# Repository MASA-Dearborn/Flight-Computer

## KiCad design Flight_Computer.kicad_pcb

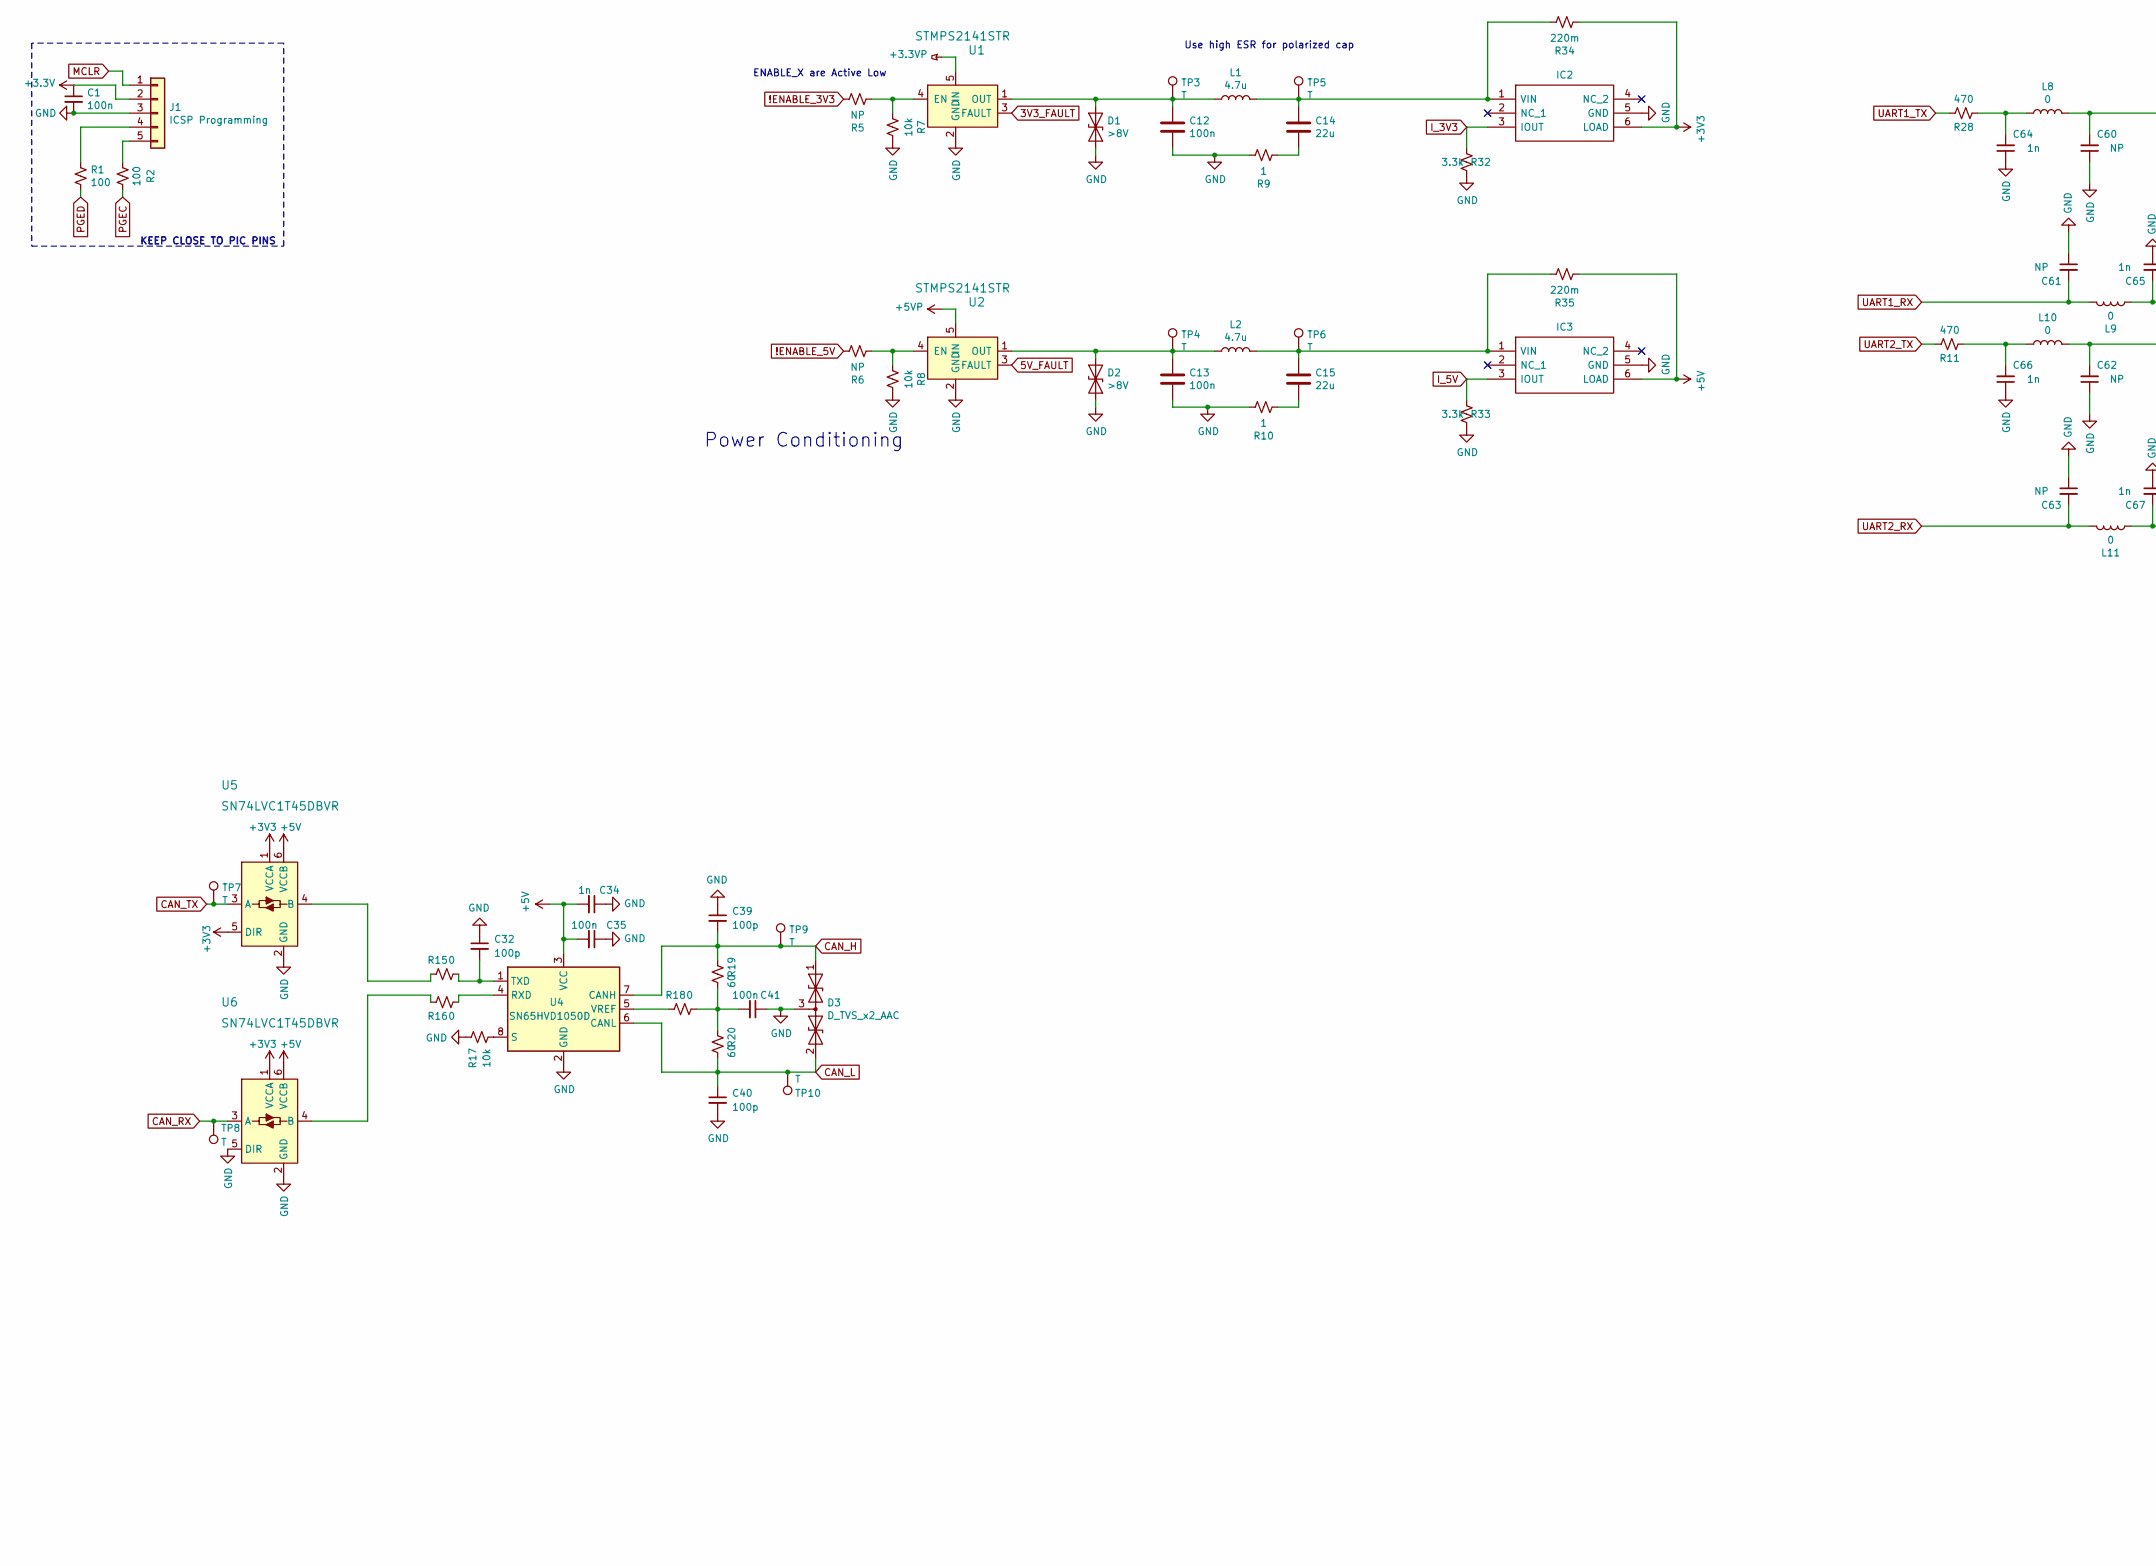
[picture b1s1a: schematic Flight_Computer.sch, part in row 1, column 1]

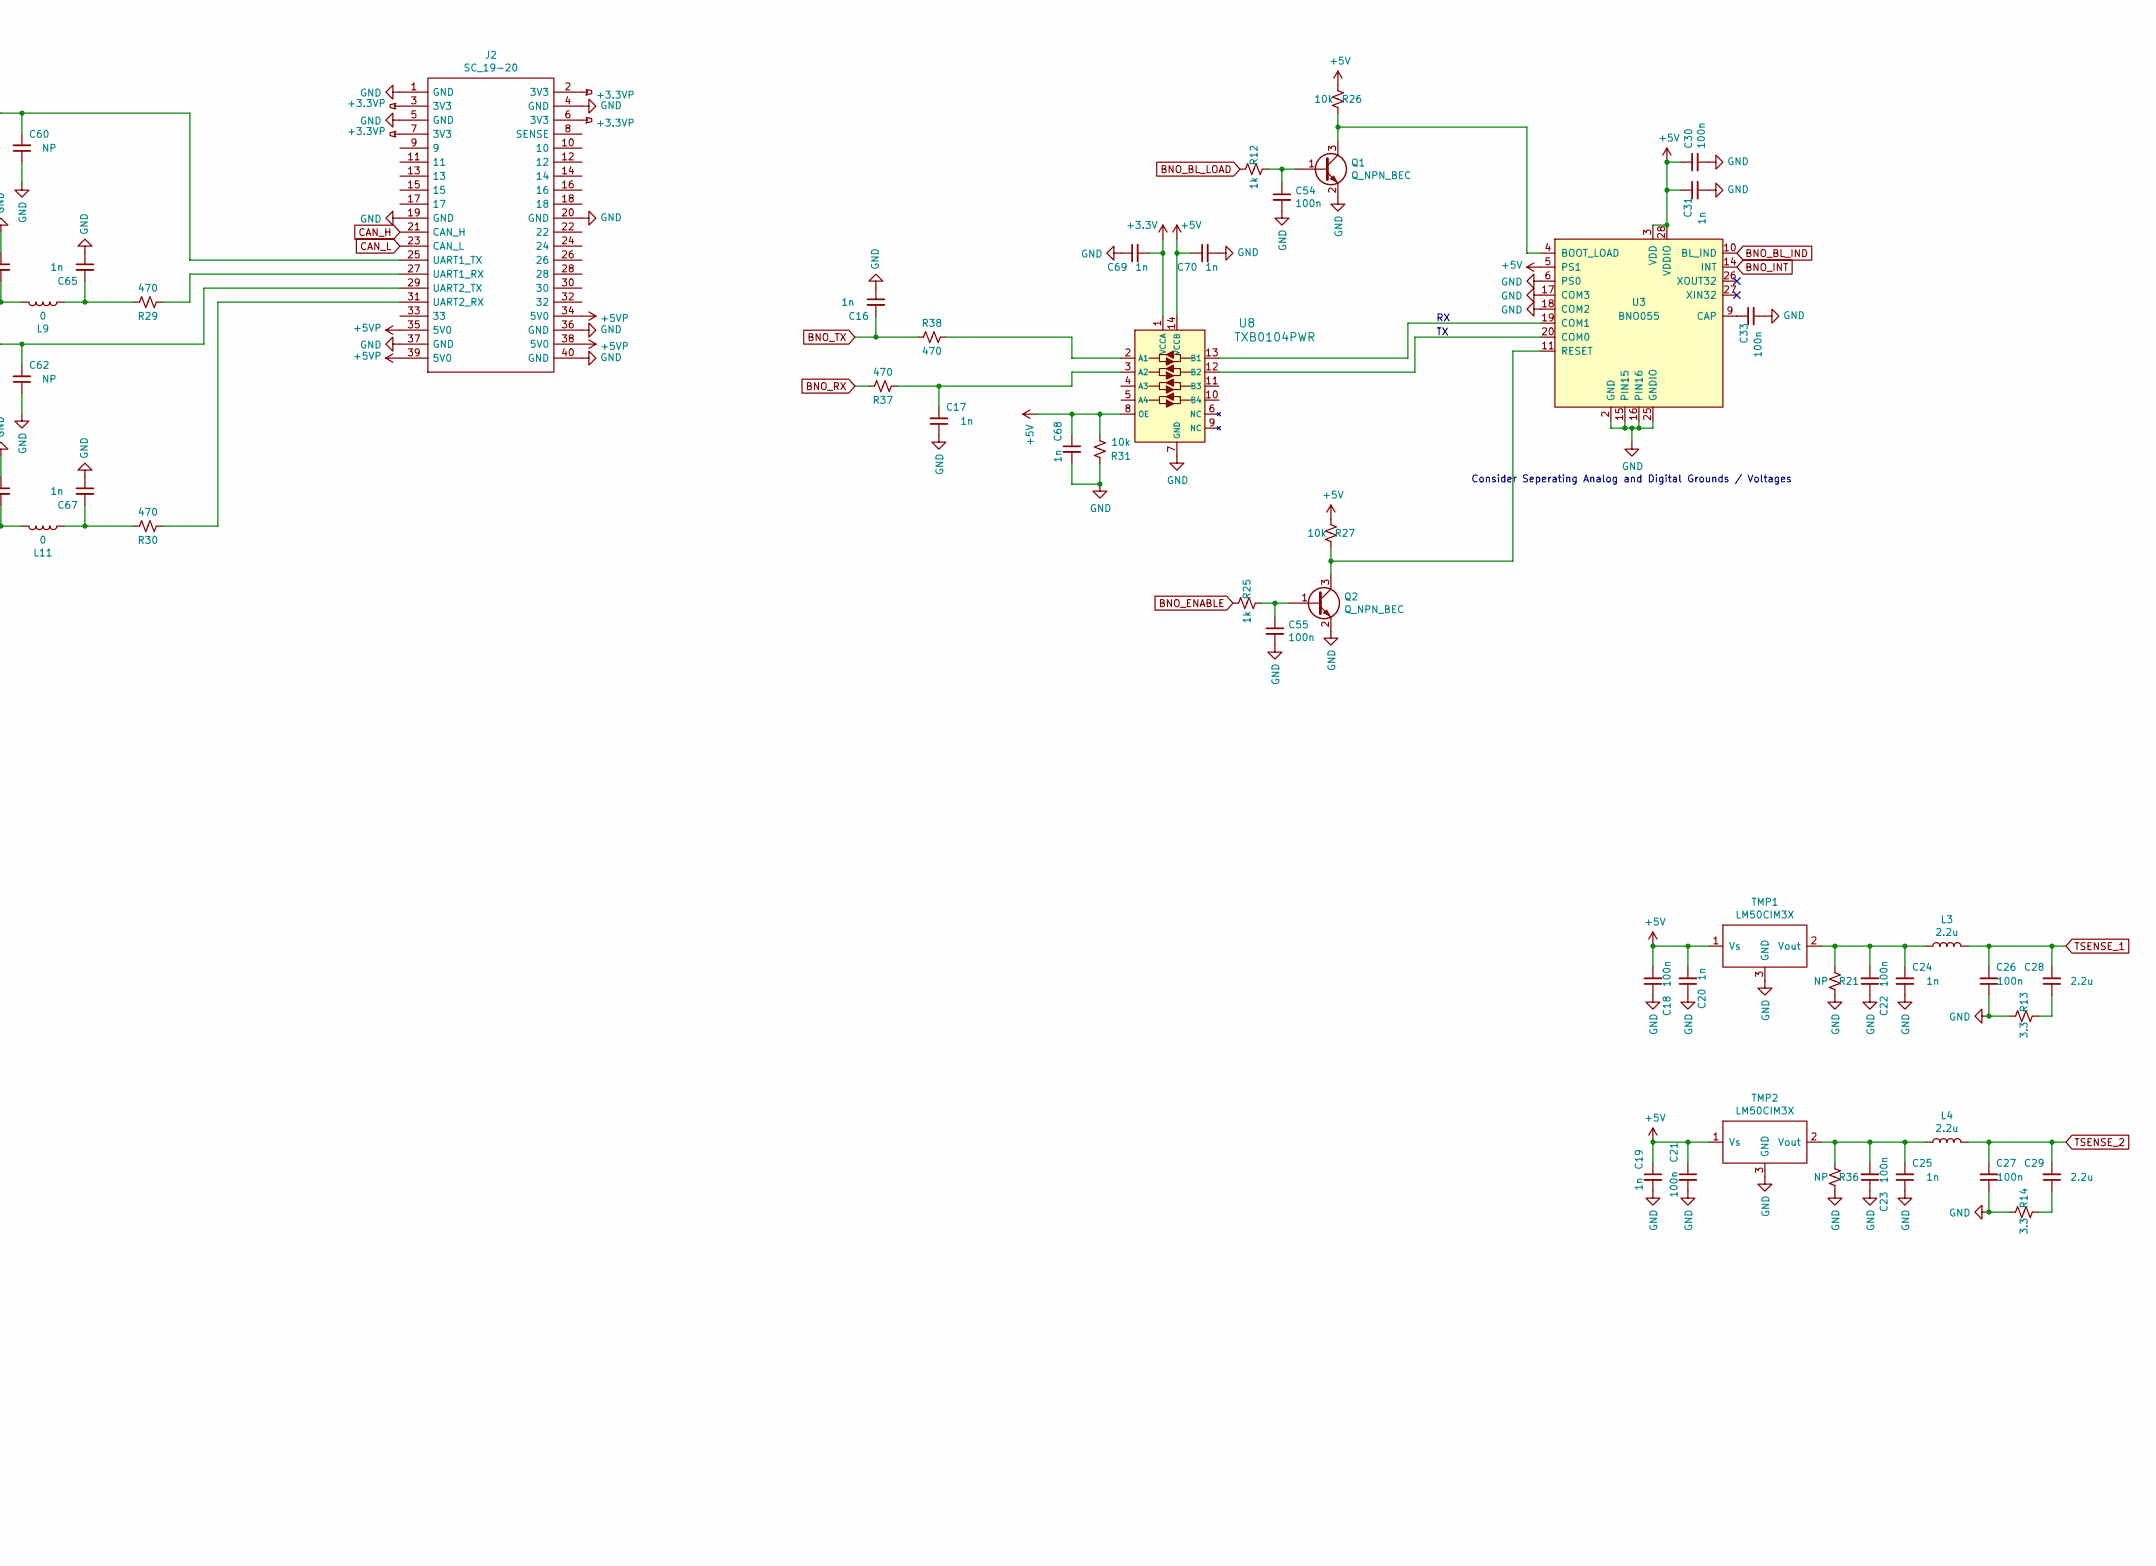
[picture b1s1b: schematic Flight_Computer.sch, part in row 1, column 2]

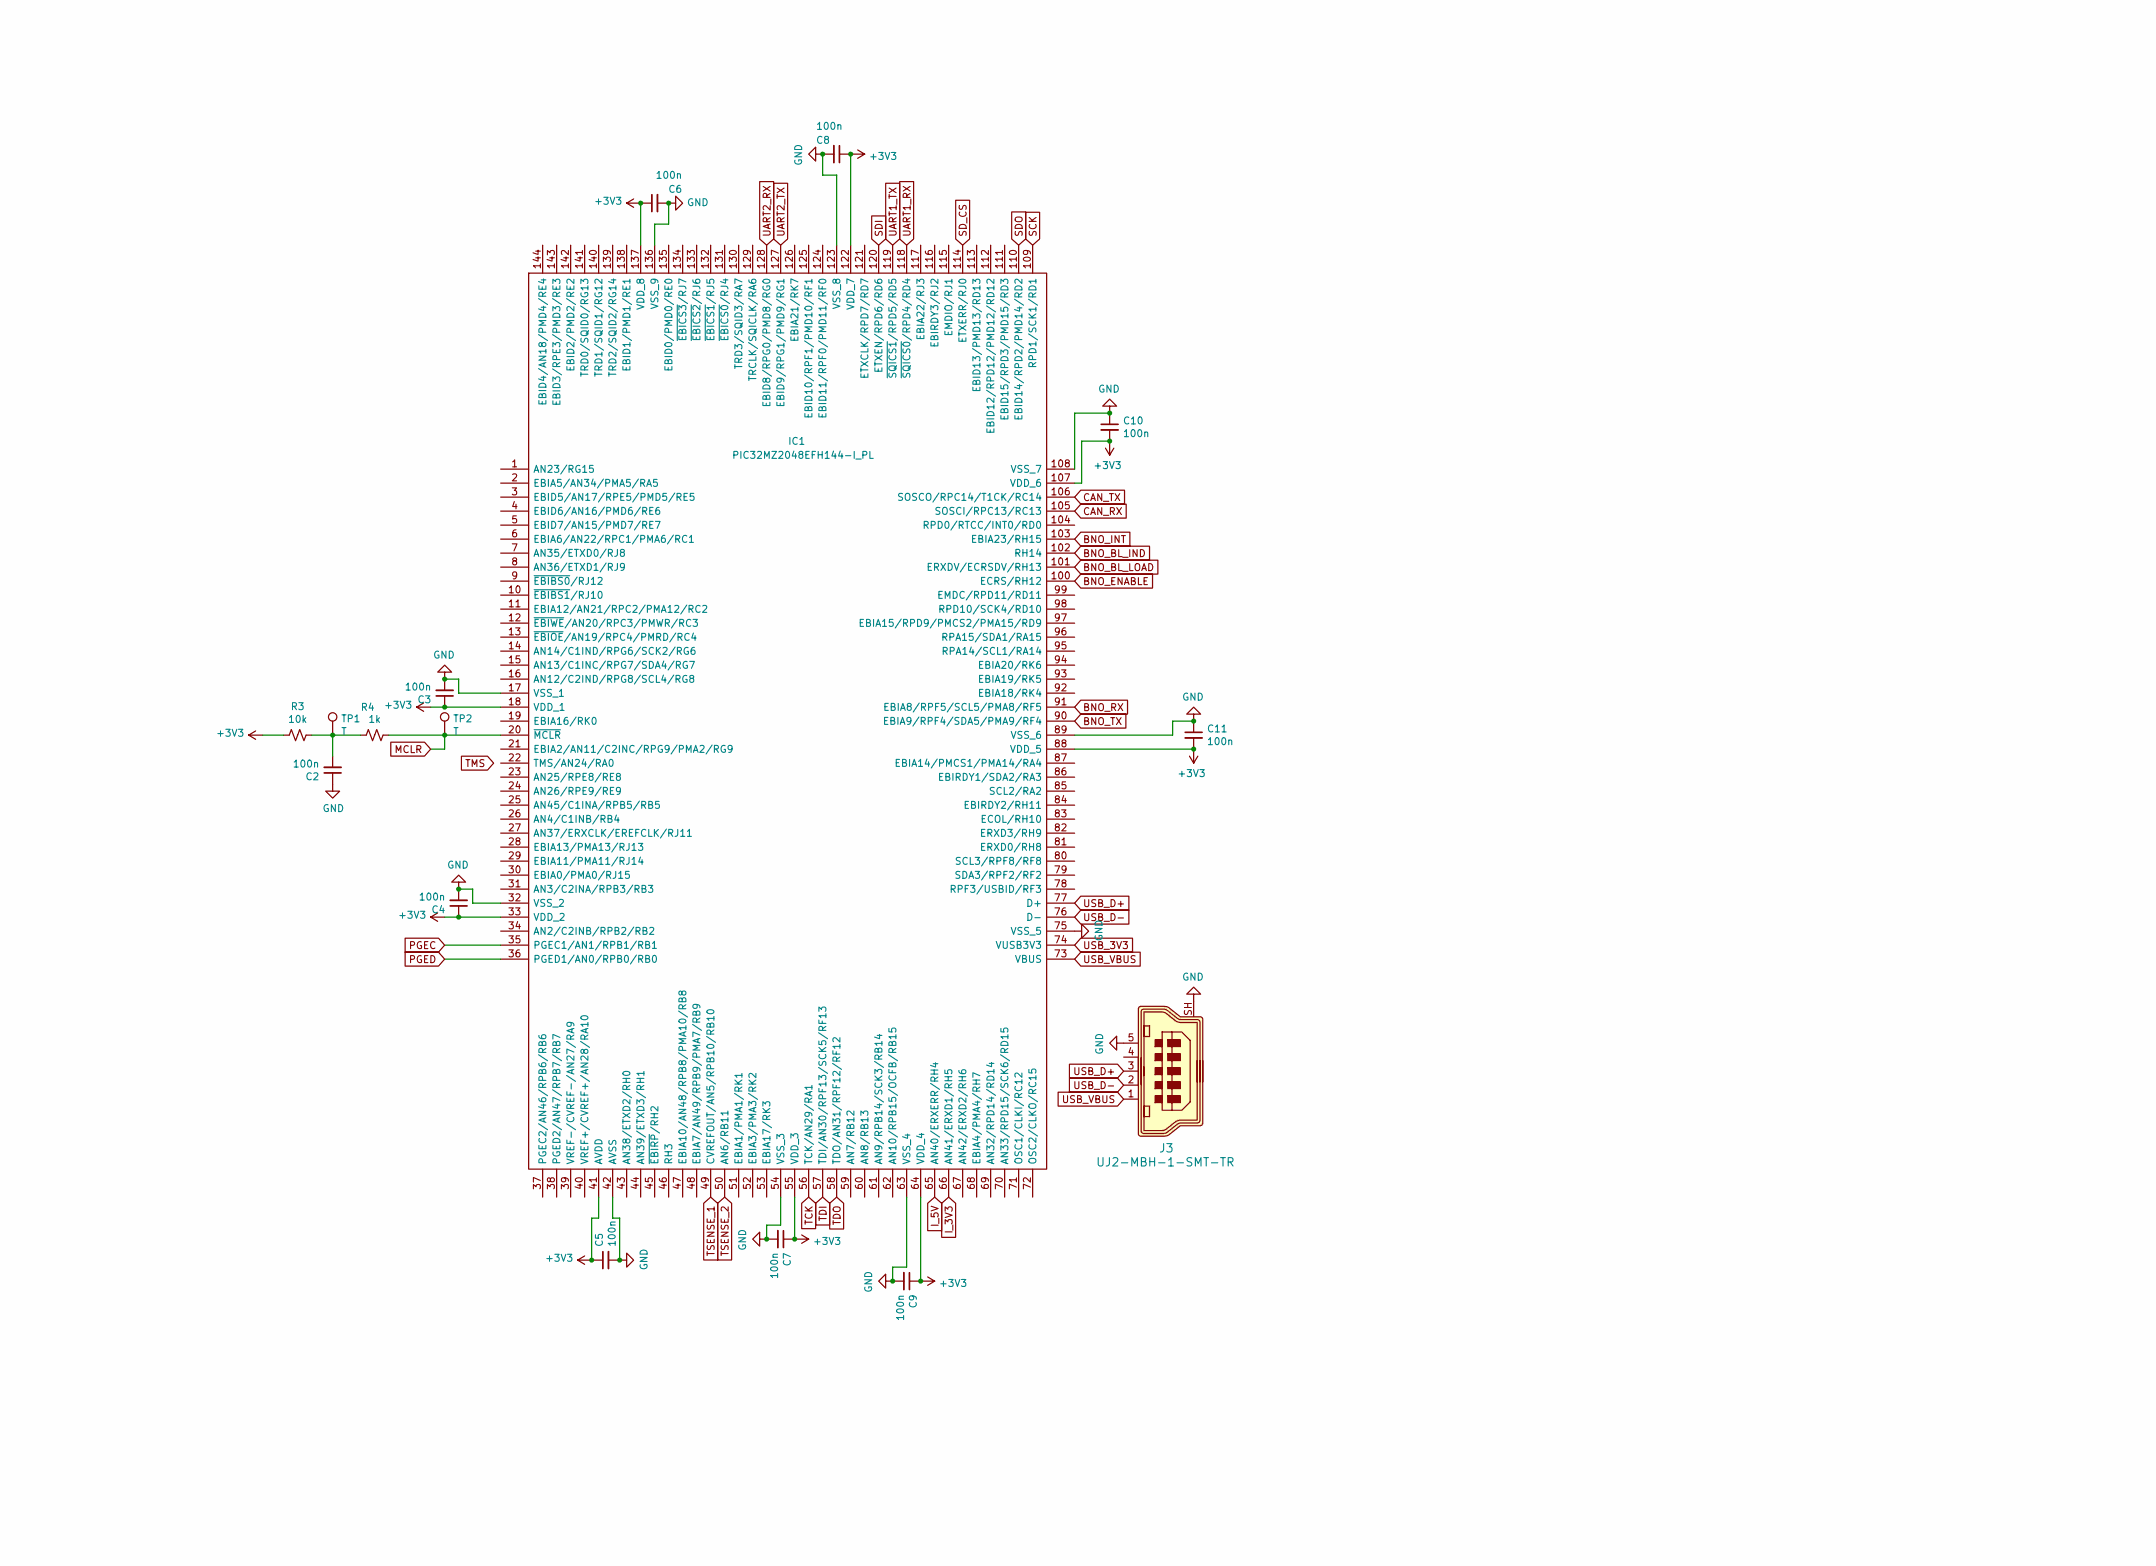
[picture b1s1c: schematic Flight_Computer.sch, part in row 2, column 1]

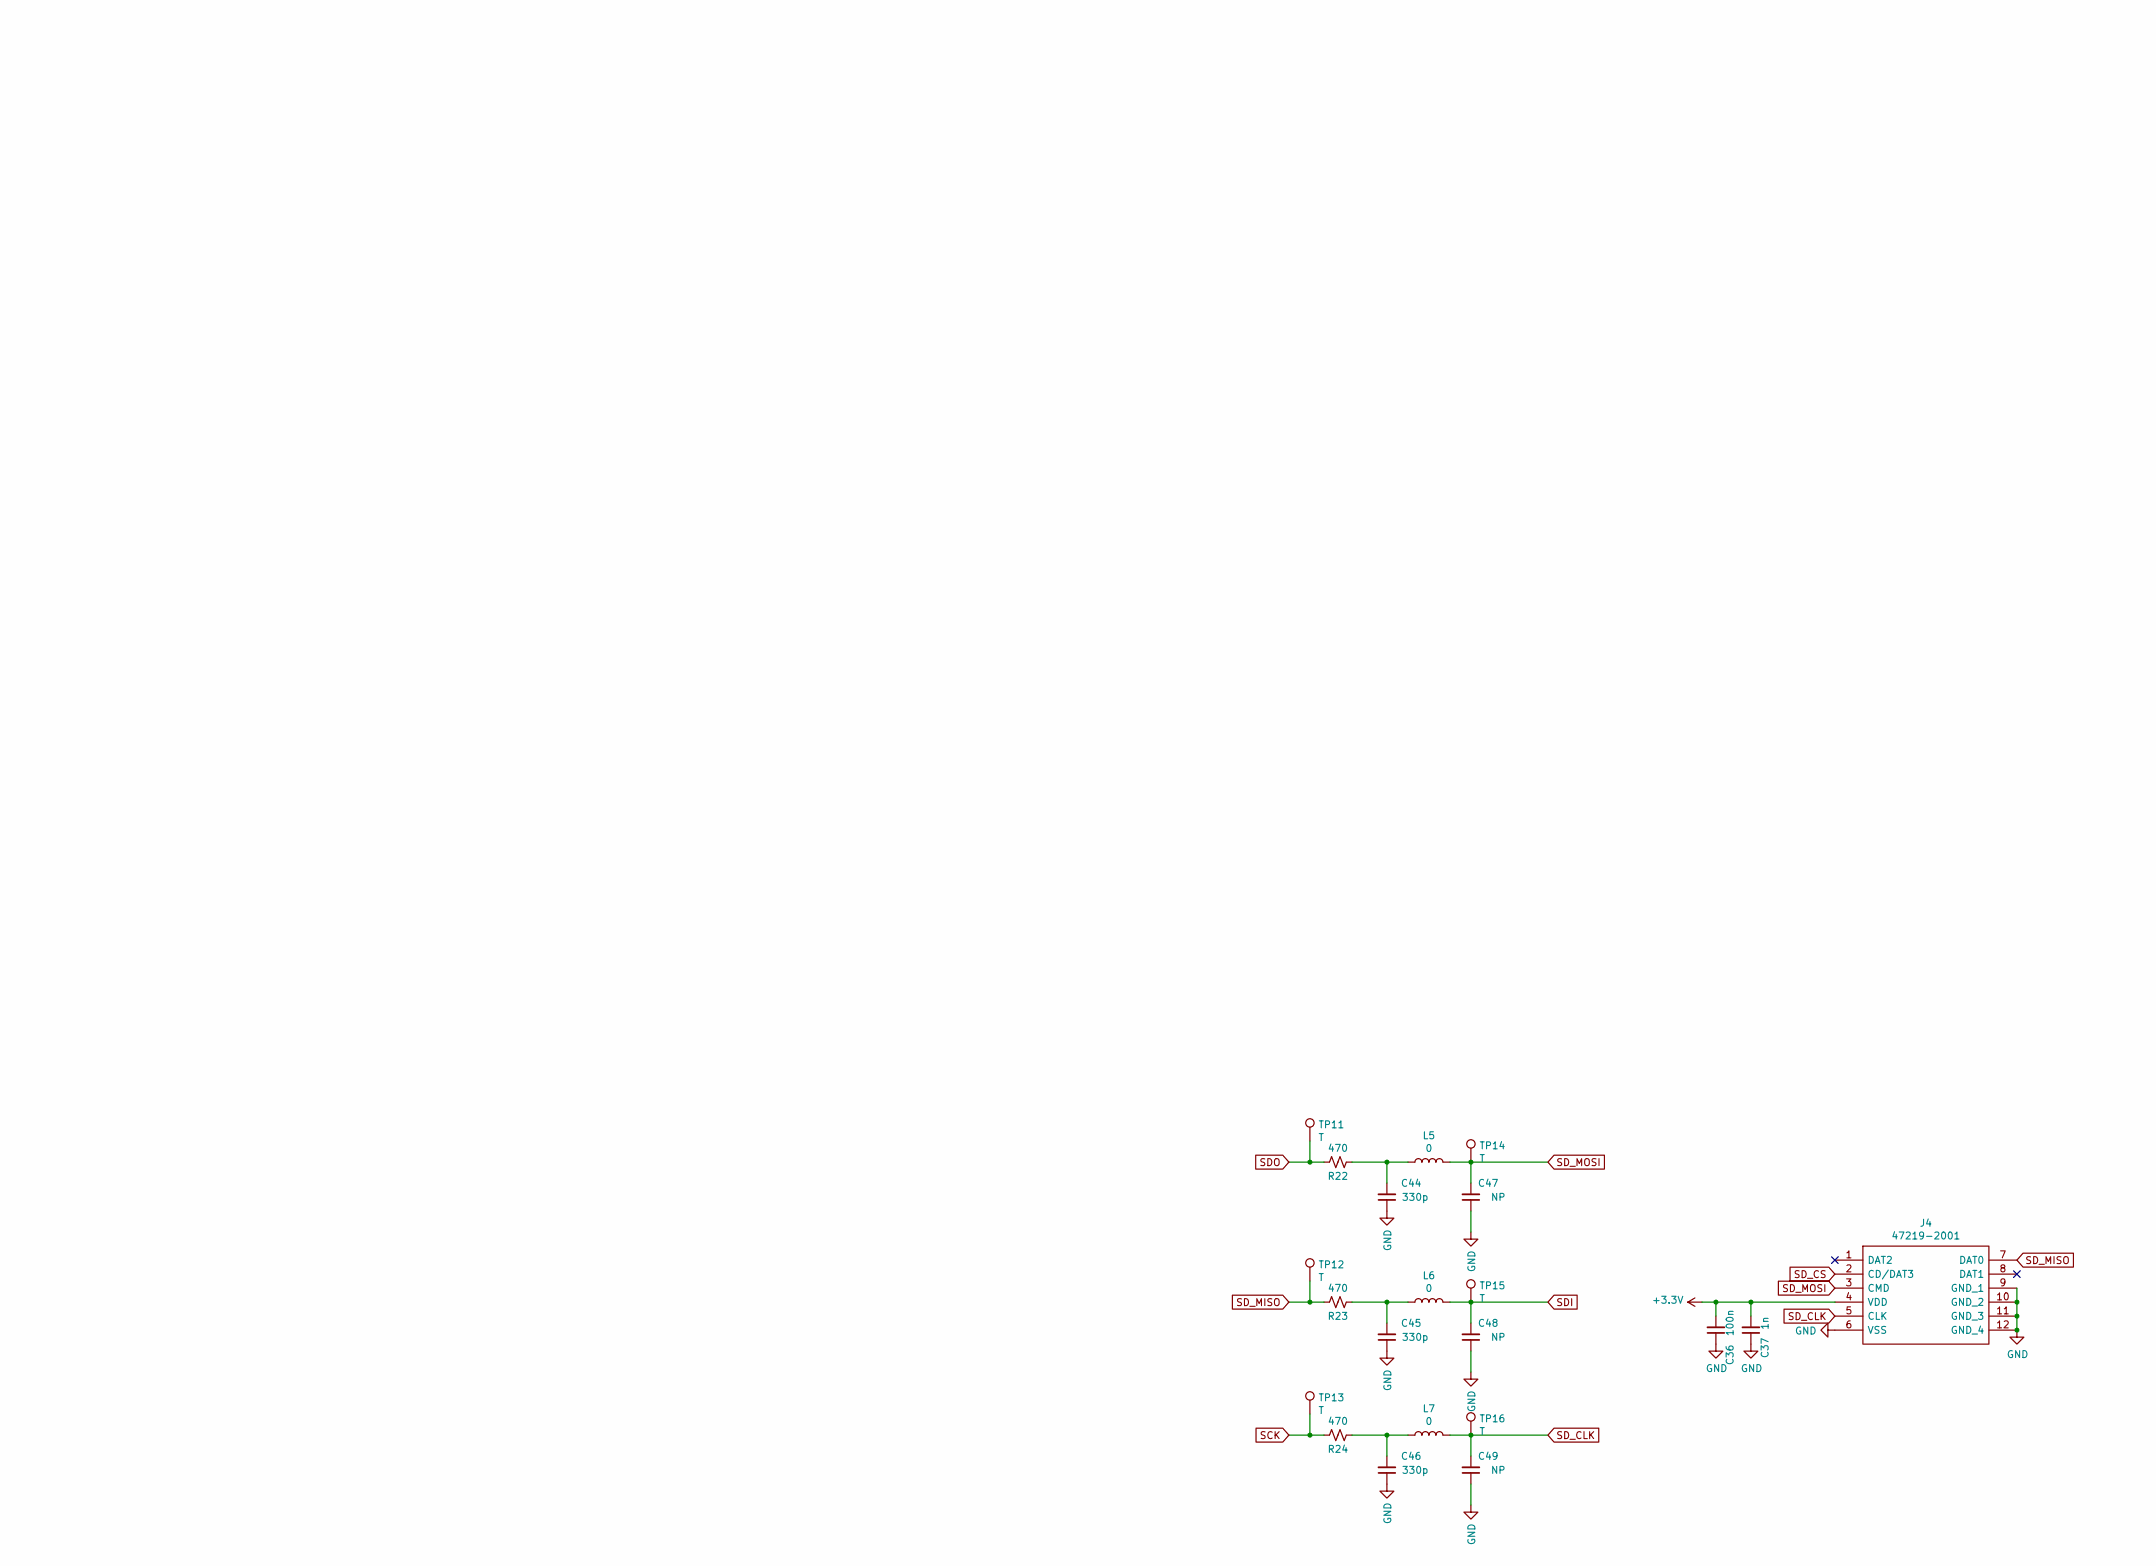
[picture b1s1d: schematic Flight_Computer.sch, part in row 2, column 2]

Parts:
C1, C2, C3, C4, C5, C6, C7, C8, C9, C10, C11, C12, C13, C18, C21, C22, C23, C26, C27, C30, C33, C35, C36, C41, C54, C55: 100n; C_0402_1005Metric
C14, C15: 22u; C_0805_2012Metric
C16, C17, C19, C20, C24, C25, C31, C34, C37, C64, C65, C66, C67, C68, C69, C70: 1n; C_0402_1005Metric
C28, C29: 2.2u; C_0402_1005Metric
C32, C39, C40: 100p; C_0402_1005Metric
C44, C45, C46: 330p; C_0402_1005Metric
C47, C48, C49, C60, C61, C62, C63: NP; C_0402_1005Metric
D1, D2: >8V; D_0805_2012Metric
D3: D_TVS_x2_AAC; SOT-23
IC1: PIC32MZ2048EFH144-I_PL; QFP50P2200X2200X160-144N; Mouser Part Number 579-MZ2048EFH144IPL
IC2, IC3: FAN4010IL6X_F113; 6-LEAD_MICROPAK; Manufacturer_Part_Number FAN4010IL6X_F113; Mouser Part Number 512-FAN4010IL6X_F113
J1: ICSP Programming; PinHeader_1x05_P2.54mm_Vertical
J2: SC_19-20; Stack_Connector_2019_2020; Manufacturer_Part_Number TFC-120-32-F-D-A-K-TR
J3: UJ2-MBH-1-SMT-TR; USB_Mini_B_Female_UJ2-MBH-1-SMT-TR; MPN UJ2-MBH-1-SMT-TR; Digi-Key_PN 102-4003-1-ND
J4: 47219-2001; 472192001; Mouser Part Number 538-47219-2001
L1: 4.7u; C_0805_2012Metric; PART# 74438324033; Digi-Key_PN 732-5684-1-ND
L2: 4.7u; L_0805_2012Metric; MPN 74438324033; Digi-Key_PN 732-5684-1-ND
L3, L4: 2.2u; L_0402_1005Metric
L5, L6, L7, L8, L9, L10, L11: 0; L_0402_1005Metric
Q1, Q2: Q_NPN_BEC; SOT-23
R1, R2: 100; R_0402_1005Metric
R3, R7, R8, R17, R26, R27, R31: 10k; R_0402_1005Metric
R4, R12, R25: 1k; R_0402_1005Metric
R5, R6, R21, R36: NP; R_0402_1005Metric
R9, R10: 1; R_0402_1005Metric
R11, R22, R23, R24, R28, R29, R30, R37, R38: 470; R_0402_1005Metric
R13, R14: 3.3; R_0402_1005Metric
R15, R16, R18: 0; R_0402_1005Metric
R19, R20: 60; R_0603_1608Metric
R32, R33: 3.3k; R_0402_1005Metric
R34, R35: 220m; R_0805_2012Metric
TMP1, TMP2: LM50CIM3X; SOT-23
TP1, TP2, TP3, TP4, TP5, TP6, TP7, TP8, TP9, TP10: T; TestPoint_Pad_1.0x1.0mm
TP11, TP12, TP13, TP14, TP15, TP16: T; TestPoint_Pad_D1.0mm
U1, U2: STMPS2141STR; SOT-753; MPN STMPS2141STR; Digi-Key_PN 497-6933-1-ND
U3: BNO055; LGA-28_5.2x3.8mm_BNO0055; MPN BNO055; Digi-Key_PN 828-1058-1-ND
U4: SN65HVD1050D; SOIC-8_3.9x4.9mm_P1.27mm
U5, U6: SN74LVC1T45DBVR; SOT-23-6; MPN SN74LVC1T45DBVR; Digi-Key_PN 296-16843-1-ND
U8: TXB0104PWR; TSSOP-14_W4.4mm; MPN TXB0104PWR; Digi-Key_PN 296-21929-1-ND

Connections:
3V3_FAULT: U1.3 (FAULT)
5V_FAULT: U2.3 (FAULT)
!ENABLE_3V3: R5.1
!ENABLE_5V: R6.1
+3.3VP: J2.2 (3V3), J2.3 (3V3), J2.6 (3V3), J2.7 (3V3), U1.5 (IN)
+5V: C18.2, C19.1, C20.2, C21.1, C30.1, C31.1, C34.2, C35.2, C68.1, C70.1, IC3.6 (LOAD), R26.2, R27.2, R31.2, R35.2, TMP1.1 (Vs), TMP2.1 (Vs), U3.3 (VDD), U3.5 (PS1), U3.28 (VDDIO), U4.3 (VCC), U5.6 (VCCB), U6.6 (VCCB), U8.8 (OE), U8.14 (VCCB)
+5VP: J2.34 (5V0), J2.35 (5V0), J2.38 (5V0), J2.39 (5V0), U2.5 (IN)
BNO_BL_IND: IC1.102 (RH14), U3.10 (BL_IND)
BNO_BL_LOAD: IC1.101 (ERXDV/ECRSDV/RH13), R12.2
BNO_ENABLE: IC1.100 (ECRS/RH12), R25.2
BNO_INT: IC1.103 (EBIA23/RH15), U3.14 (INT)
BNO_RX: IC1.91 (EBIA8/RPF5/SCL5/PMA8/RF5), R37.1
BNO_TX: C16.2, IC1.90 (EBIA9/RPF4/SDA5/PMA9/RF4), R38.2
CAN_H: C39.2, D3.1 (A1), J2.21 (CAN_H), R19.1, TP9.1, U4.7 (CANH)
CAN_L: C40.1, D3.2 (A2), J2.23 (CAN_L), R20.2, TP10.1, U4.6 (CANL)
CAN_RX: IC1.105 (SOSCI/RPC13/RC13), TP8.1, U6.3 (A)
CAN_TX: IC1.106 (SOSCO/RPC14/T1CK/RC14), TP7.1, U5.3 (A)
GND: C1.2, C2.1, C3.2, C4.2, C5.2, C6.2, C7.2, C8.2, C9.2, C10.1, C11.1, C12.2, C13.2, C16.1, C17.1, C18.1, C19.2, C20.1, C21.2, C22.1, C23.1, C24.1, C25.1, C26.1, C27.1, C30.2, C31.2, C32.1, C33.2, C34.1, C35.1, C36.1, C37.1, C39.1, C40.2, C41.1, C44.1, C45.1, C46.1, C47.1, C48.1, C49.1, C54.2, C55.2, C60.1, C61.1, C62.1, C63.1, C64.1, C65.1, C66.1, C67.1, C68.2, C69.1, C70.2, D1.1 (A1), D2.1 (A1), D3.3 (common), IC1.17 (VSS_1), IC1.32 (VSS_2), IC1.42 (AVSS), IC1.54 (VSS_3), IC1.63 (VSS_4), IC1.75 (VSS_5), IC1.89 (VSS_6), IC1.108 (VSS_7), IC1.123 (VSS_8), IC1.136 (VSS_9), IC2.5 (GND), IC3.5 (GND), J1.3, J2.1 (GND), J2.4 (GND), J2.5 (GND), J2.19 (GND), J2.20 (GND), J2.36 (GND), J2.37 (GND), J2.40 (GND), J3.5, J3.SH, J4.6 (VSS), J4.9 (GND_1), J4.10 (GND_2), J4.11 (GND_3), J4.12 (GND_4), Q1.2 (E), Q2.2 (E), R7.1, R8.1, R9.1, R10.1, R13.2, R14.2, R17.1, R21.1, R31.1, R32.1, R33.1, R36.1, TMP1.3 (GND), TMP2.3 (GND), U1.2 (GND), U2.2 (GND), U3.2 (GND), U3.6 (PS0), U3.15 (PIN15), U3.16 (PIN16), U3.17 (COM3), U3.18 (COM2), U3.25 (GNDIO), U4.2 (GND), U5.2 (GND), U6.2 (GND), U6.5 (DIR), U8.7 (GND)
I_3V3: IC1.66 (AN41/ERXD1/RH5), IC2.3 (IOUT), R32.2
I_5V: IC1.65 (AN40/ERXERR/RH4), IC3.3 (IOUT), R33.2
MCLR: IC1.20 (~MCLR), J1.1, R4.1, TP2.1
unnamed: C2.2, R3.1, R4.2, TP1.1
unnamed: C12.1, D1.2 (A2), L1.1, TP3.1, U1.1 (OUT)
unnamed: C13.1, D2.2 (A2), L2.1, TP4.1, U2.1 (OUT)
unnamed: C14.1, IC2.1 (VIN), L1.2, R34.1, TP5.1
unnamed: C14.2, R9.2
unnamed: C15.1, IC3.1 (VIN), L2.2, R35.1, TP6.1
unnamed: C15.2, R10.2
unnamed: C17.2, R37.2, U8.3 (A2)
unnamed: C22.2, C24.2, L3.1, R21.2, TMP1.2 (Vout)
unnamed: C23.2, C25.2, L4.1, R36.2, TMP2.2 (Vout)
unnamed: C28.1, R13.1
unnamed: C29.1, R14.1
unnamed: C32.2, R15.2, U4.1 (TXD)
unnamed: C33.1, U3.9 (CAP)
unnamed: C41.2, R18.2, R19.2, R20.1
unnamed: C44.2, L5.1, R22.2
unnamed: C45.2, L6.1, R23.2
unnamed: C46.2, L7.1, R24.2
unnamed: C54.1, Q1.1 (B), R12.1
unnamed: C55.1, Q2.1 (B), R25.1
unnamed: C60.2, J2.25 (UART1_TX), L8.2
unnamed: C62.2, J2.29 (UART2_TX), L10.2
unnamed: C64.2, L8.1, R28.2
unnamed: C65.2, L9.1, R29.1
unnamed: C66.2, L10.1, R11.2
unnamed: C67.2, L11.1, R30.1
unnamed: J1.4, R1.2
unnamed: J1.5, R2.1
unnamed: J2.27 (UART1_RX), R29.2
unnamed: J2.31 (UART2_RX), R30.2
unnamed: Q1.3 (C), R26.1, U3.4 (BOOT_LOAD)
unnamed: Q2.3 (C), R27.1, U3.11 (RESET)
unnamed: R5.2, R7.2, U1.4 (EN)
unnamed: R6.2, R8.2, U2.4 (EN)
unnamed: R15.1, U5.4 (B)
unnamed: R16.1, U6.4 (B)
unnamed: R16.2, U4.4 (RXD)
unnamed: R17.2, U4.8 (S)
unnamed: R18.1, U4.5 (VREF)
unnamed: R38.1, U8.2 (A1)
unnamed: U3.19 (COM1), U8.13 (B1)
unnamed: U3.20 (COM0), U8.12 (B2)
PGEC: IC1.35 (PGEC1/AN1/RPB1/RB1), R2.2
PGED: IC1.36 (PGED1/AN0/RPB0/RB0), R1.1
SCK: IC1.109 (RPD1/SCK1/RD1), R24.1, TP13.1
SDI: C48.2, IC1.120 (ETXEN/RPD6/RD6), L6.2, TP15.1
SDO: IC1.110 (EBID14/RPD2/PMD14/RD2), R22.1, TP11.1
SD_CLK: C49.2, J4.5 (CLK), L7.2, TP16.1
SD_CS: IC1.114 (ETXERR/RJ0), J4.2 (CD/DAT3)
SD_MISO: J4.7 (DAT0), R23.1, TP12.1
SD_MOSI: C47.2, J4.3 (CMD), L5.2, TP14.1
TCK: IC1.56 (TCK/AN29/RA1)
TDI: IC1.57 (TDI/AN30/RPF13/SCK5/RF13)
TDO: IC1.58 (TDO/AN31/RPF12/RF12)
TSENSE_1: C26.2, C28.2, IC1.49 (CVREFOUT/AN5/RPB10/RB10), L3.2
TSENSE_2: C27.2, C29.2, IC1.50 (AN6/RB11), L4.2
UART1_RX: C61.2, IC1.118 (~SQICS0~/RPD4/RD4), L9.2
UART1_TX: IC1.119 (~SQICS1~/RPD5/RD5), R28.1
UART2_RX: C63.2, IC1.128 (EBID8/RPG0/PMD8/RG0), L11.2
UART2_TX: IC1.127 (EBID9/RPG1/PMD9/RG1), R11.1
USB_3V3: IC1.74 (VUSB3V3)
USB_D+: IC1.77 (D+), J3.3
USB_D-: IC1.76 (D-), J3.2
USB_VBUS: IC1.73 (VBUS), J3.1

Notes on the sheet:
KEEP CLOSE TO PIC PINS
Use high ESR for polarized cap
ENABLE_X are Active Low
Power Conditioning
Consider Seperating Analog and Digital Grounds / Voltages

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
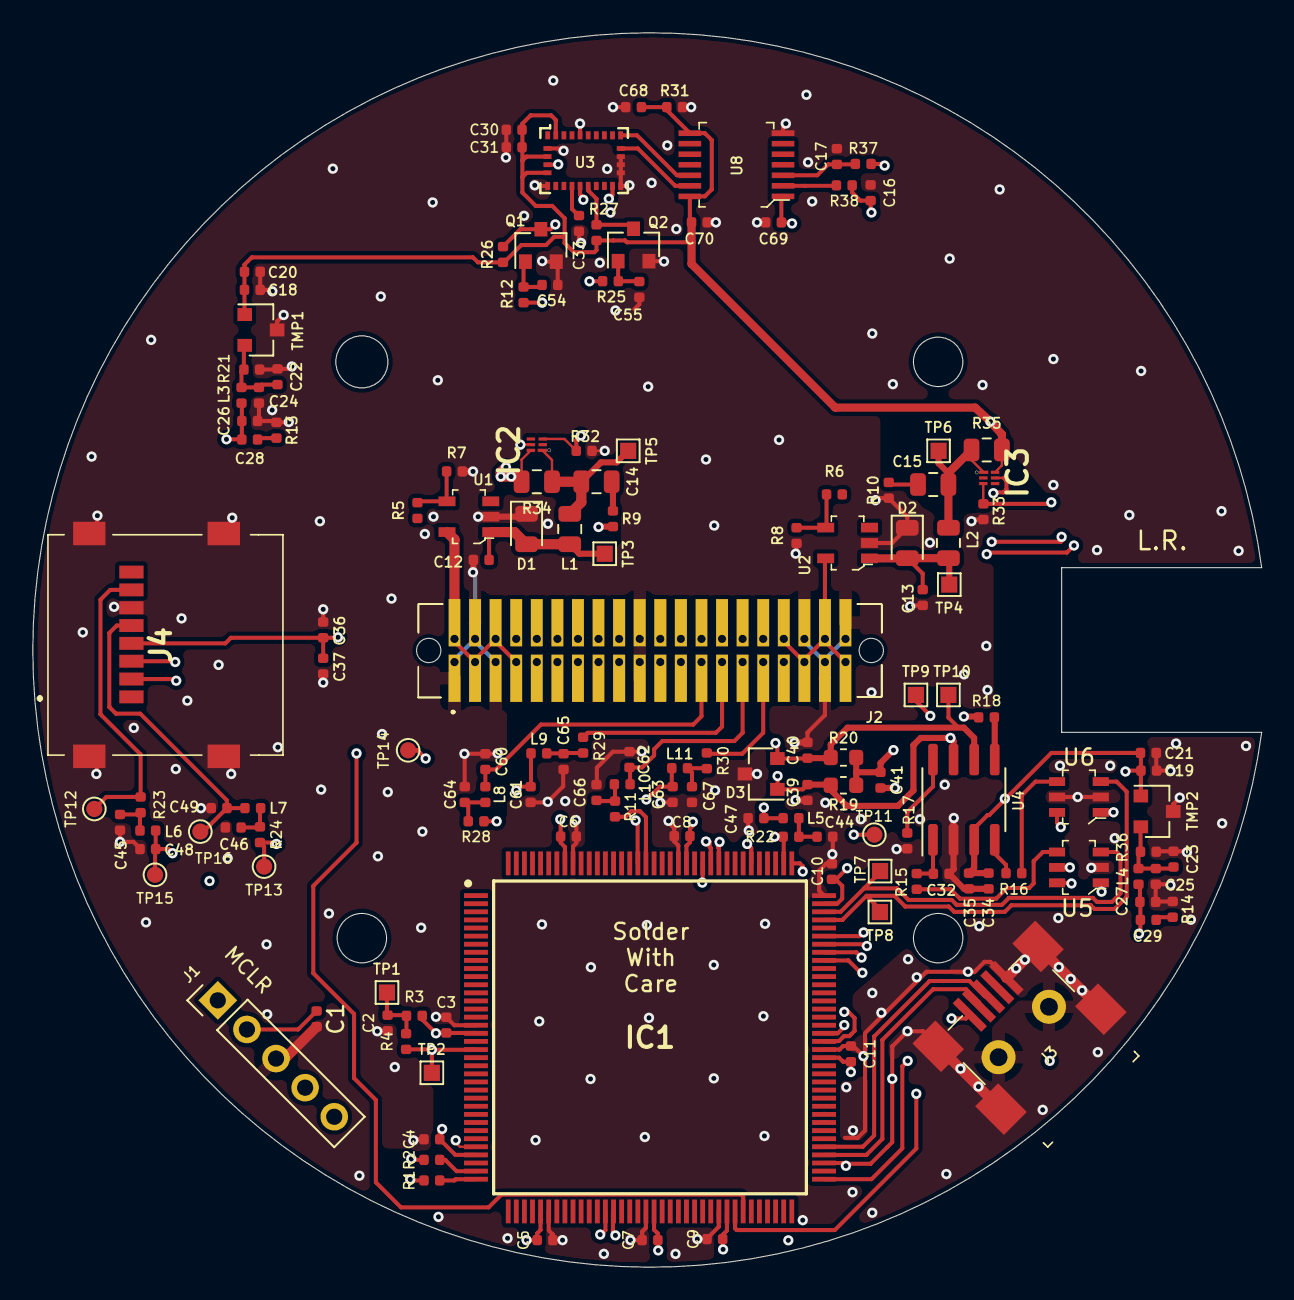
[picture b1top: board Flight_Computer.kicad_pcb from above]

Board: 4 copper layers, 75.8 x 76.2 mm, 145 parts (0 on the bottom side), 78 nets.

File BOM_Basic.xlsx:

C1-C13, C18, C21-C23, C26, C27, C30, C33, C35, C36, C41, C54, C55 | 100n | 0402_C
C14, C15 | 22u | 0805_C
C28, C29 | 2.2u | 0402_C
C19, C20, C24, C25, C31, C34, C37, C44-C46, C64-C70 | 1n | 0402_C
C32, C39, C40 | 100p | 0402_C
C50-C52, C56-C59 | 1u | 0402_C
C47-C49, C60-C63 | 10n | 0402_C
L1 | 4.7u | 0805_C
L2 | 4.7u | 0805_L
L3, L4 | 2.2u | 0402_L
L5-L11 | 220n | 0402_L
R1, R2 | 100 | 0402_R
R3, R7, R8, R17, R26, R27, R31 | 10k | 0402_R
R4, R12, R25 | 1k | 0402_R
R5, R6 | NP | 0402_R
R9, R10 | 1 | 0402_R
R11, R13, R14, R22-R24, R28-R30 | 3.3 | 0402_R
R15, R16, R18 | 0 | 0402_R
R19, R20 | 60 | 0603_R
R21, R32, R33, R36 | 3.3k | 0402_R
R34, R35 | 220m | 0805_R

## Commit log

2019-12-22 Added SD card, CAN interface, many more updates. Also introduced PCB Template
2019-12-24 Many changes
2019-12-28 Routing progress
2019-12-28 More additions
2019-12-29 Finished routing
2019-12-29 3D finished
2019-12-30 Fixed CAN Bus voltage error
2019-12-30 Gerbers added
2020-01-12 Gerbers
2020-01-24 Major changes to routing and fixed filters
2020-02-19 Adjusted a few vias to satisfy DRC
2020-02-20 Fixed Vias
